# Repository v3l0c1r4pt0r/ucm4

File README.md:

# uCM4

Raspberry Pi Compute Module 4 micro carrier board

# Features

* exactly same size as CM4
* support for both Lite and eMMC variants of CM4
* Gigabit Ethernet
* microSD slot (optional)
* Micro USB for power and USB 2.0 data transfer
* USB-OTG support

# Table of contents

1. [Customizations](customizations.md)
2. [Troubleshooting](troubleshooting.md)

# Project page

Complete project page with pictures, updates and so on, is available at
[Hackaday.io](https://hackaday.io/project/179793-ucm4).

# License

This work is licensed under a [Creative Commons Attribution 4.0 International License][cc-by].

You can use it for anything as long as you preserve license file and author information in source distribution and authorship information on PCB. Derived work should mention original author in same locations as this repository.

[![CC BY 4.0][cc-by-image]][cc-by]

[cc-by]: http://creativecommons.org/licenses/by/4.0/
[cc-by-image]: https://i.creativecommons.org/l/by/4.0/88x31.png

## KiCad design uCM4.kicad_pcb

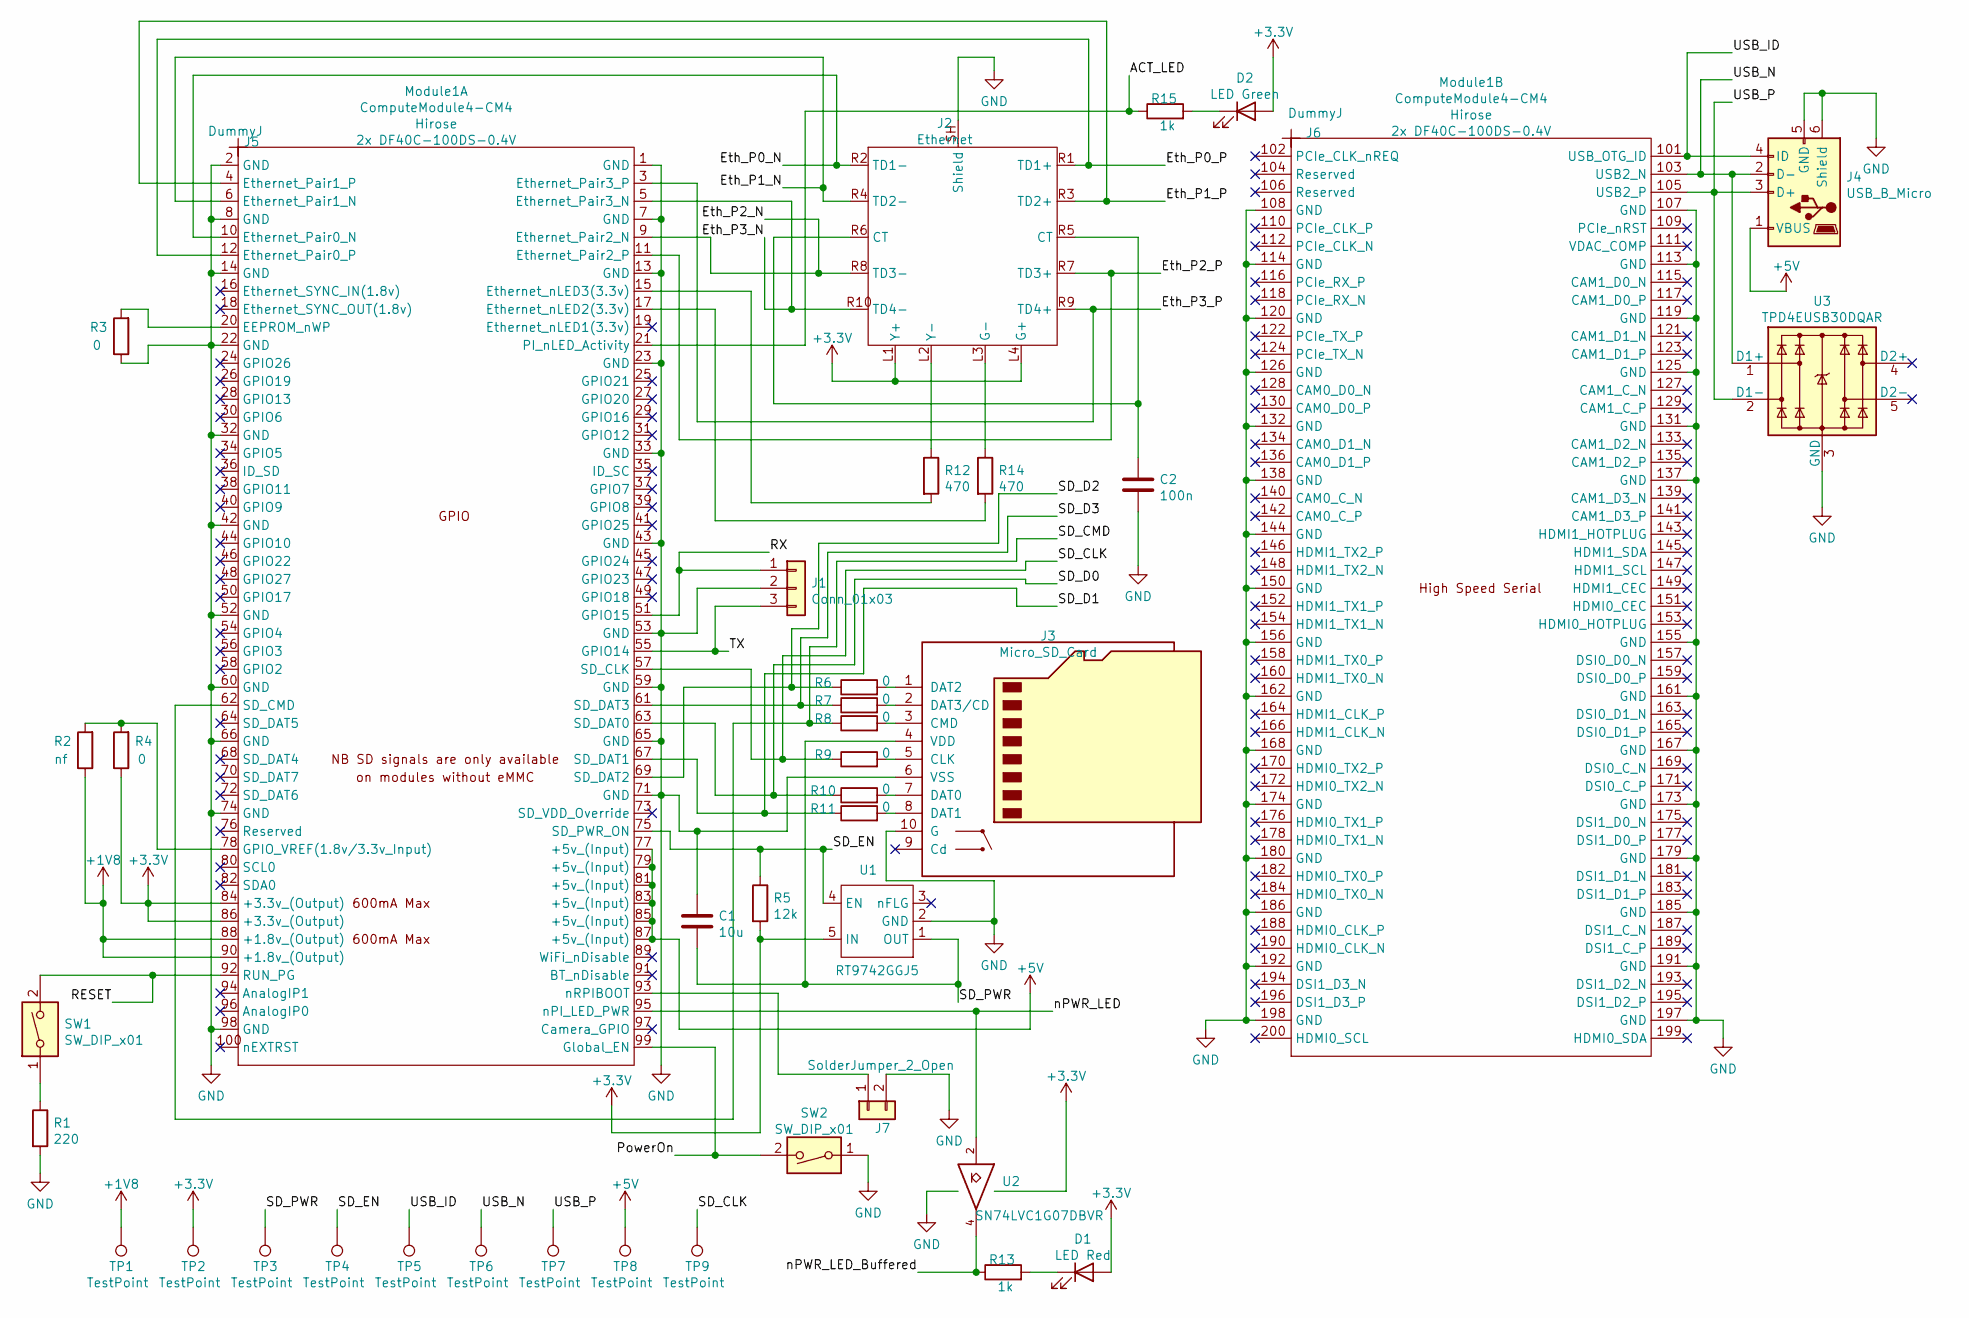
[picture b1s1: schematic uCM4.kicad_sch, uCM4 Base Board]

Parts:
C1: 10u; C_0603_1608Metric_Pad1.08x0.95mm_HandSolder; LCSC# C326057
C2: 100n; C_0603_1608Metric_Pad1.08x0.95mm_HandSolder; LCSC# C108079
D1: LED Red; LED_0603_1608Metric_Pad1.05x0.95mm_HandSolder; LCSC# C181863
D2: LED Green; LED_0603_1608Metric_Pad1.05x0.95mm_HandSolder; LCSC# C72043
J1: Conn_01x03; PinHeader_1x03_P2.54mm_Vertical; LCSC# C49257
J2: Ethernet; RB1-2S5BAK1A; LCSC# C363232
J3: Micro_SD_Card; TF-015; LCSC# C113206
J4: USB_B_Micro; U254-05XX-4BH81; LCSC# C2682232
J5, J6: DummyJ; LCSC# C424649
J7: SolderJumper_2_Open; PinHeader_1x02_P2.54mm_Vertical
Module1: ComputeModule4-CM4; Raspberry-Pi-4-Compute-Module; LCSC# C424649
R1: 220; R_0603_1608Metric_Pad0.98x0.95mm_HandSolder; LCSC# C22962
R2: nf; R_0603_1608Metric_Pad0.98x0.95mm_HandSolder
R3, R4: 0; R_0603_1608Metric_Pad0.98x0.95mm_HandSolder; LCSC# C21189
R5: 12k; R_0603_1608Metric_Pad0.98x0.95mm_HandSolder; LCSC# C22790
R6, R7, R8, R9, R10, R11: 0; R_0402_1005Metric_Pad0.72x0.64mm_HandSolder; LCSC# C17168
R12, R14: 470; R_0603_1608Metric_Pad0.98x0.95mm_HandSolder; LCSC# C23179
R13, R15: 1k; R_0603_1608Metric_Pad0.98x0.95mm_HandSolder; LCSC# C21190
SW1, SW2: SW_DIP_x01; PTS840_PM_SMTR_LFS; LCSC# C221911
TP1, TP2, TP3, TP4, TP5, TP6, TP7, TP8, TP9: TestPoint; TestPoint_Pad_D1.0mm
U1: RT9742GGJ5; SOT-23-5; Part Description Power Switch/Driver 1:1 N-Channel 1A TS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; LCSC# C2693603
U2: SN74LVC1G07DBVR; SOT-23-5_HandSoldering; LCSC# C7829
U3: TPD4EUSB30DQAR; USON-10_2.5x1.0mm_P0.5mm; LCSC# C90627

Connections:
+1V8: Module1.88 (+1.8v_(Output)), Module1.90 (+1.8v_(Output)), R2.1, TP1.1
+3V3: D1.2 (A), D2.2 (A), J2.L1 (Y+), J2.L4 (G+), Module1.84 (+3.3v_(Output)), Module1.86 (+3.3v_(Output)), R4.1, R5.2, TP2.1, U1.5 (IN), U2.5 (VCC)
+5V: J4.1 (VBUS), Module1.77 (+5v_(Input)), Module1.79 (+5v_(Input)), Module1.81 (+5v_(Input)), Module1.83 (+5v_(Input)), Module1.85 (+5v_(Input)), Module1.87 (+5v_(Input)), TP8.1
/ACT_LED: Module1.21 (PI_nLED_Activity), R15.1
/Eth_P0_N: J2.R2 (TD1-), Module1.10 (Ethernet_Pair0_N)
/Eth_P0_P: J2.R1 (TD1+), Module1.12 (Ethernet_Pair0_P)
/Eth_P1_N: J2.R4 (TD2-), Module1.6 (Ethernet_Pair1_N)
/Eth_P1_P: J2.R3 (TD2+), Module1.4 (Ethernet_Pair1_P)
/Eth_P2_N: J2.R8 (TD3-), Module1.9 (Ethernet_Pair2_N)
/Eth_P2_P: J2.R7 (TD3+), Module1.11 (Ethernet_Pair2_P)
/Eth_P3_N: J2.R10 (TD4-), Module1.5 (Ethernet_Pair3_N)
/Eth_P3_P: J2.R9 (TD4+), Module1.3 (Ethernet_Pair3_P)
/PowerOn: Module1.99 (Global_EN), SW2.2
/RESET: Module1.92 (RUN_PG), SW1.2
/RX: J1.1, Module1.51 (GPIO15)
/SD_CLK: Module1.57 (SD_CLK), R9.1, TP9.1
/SD_CMD: Module1.62 (SD_CMD), R8.1
/SD_D0: Module1.63 (SD_DAT0), R10.1
/SD_D1: Module1.67 (SD_DAT1), R11.1
/SD_D2: Module1.69 (SD_DAT2), R6.1
/SD_D3: Module1.61 (SD_DAT3), R7.1
/SD_EN: Module1.75 (SD_PWR_ON), R5.1, TP4.1, U1.4 (EN)
/SD_PWR: C1.2, J3.4 (VDD), TP3.1, U1.1 (OUT)
/TX: J1.3, Module1.55 (GPIO14)
/USB_ID: J4.4 (ID), Module1.101 (USB_OTG_ID), TP5.1
/USB_N: J4.2 (D-), Module1.103 (USB2_N), TP6.1, U3.1 (D1+)
/USB_P: J4.3 (D+), Module1.105 (USB2_P), TP7.1, U3.2 (D1-)
/nPWR_LED: Module1.95 (nPI_LED_PWR), U2.2
/nPWR_LED_Buffered: R13.1, U2.4
GND: C1.1, C2.2, J1.2, J2.SH (Shield), J3.6 (VSS), J3.10 (G), J4.5 (GND), J4.6 (Shield), J7.2, Module1.1 (GND), Module1.2 (GND), Module1.7 (GND), Module1.8 (GND), Module1.13 (GND), Module1.14 (GND), Module1.22 (GND), Module1.23 (GND), Module1.32 (GND), Module1.33 (GND), Module1.42 (GND), Module1.43 (GND), Module1.52 (GND), Module1.53 (GND), Module1.59 (GND), Module1.60 (GND), Module1.65 (GND), Module1.66 (GND), Module1.71 (GND), Module1.74 (GND), Module1.98 (GND), Module1.107 (GND), Module1.108 (GND), Module1.113 (GND), Module1.114 (GND), Module1.119 (GND), Module1.120 (GND), Module1.125 (GND), Module1.126 (GND), Module1.131 (GND), Module1.132 (GND), Module1.137 (GND), Module1.138 (GND), Module1.144 (GND), Module1.150 (GND), Module1.155 (GND), Module1.156 (GND), Module1.161 (GND), Module1.162 (GND), Module1.167 (GND), Module1.168 (GND), Module1.173 (GND), Module1.174 (GND), Module1.179 (GND), Module1.180 (GND), Module1.185 (GND), Module1.186 (GND), Module1.191 (GND), Module1.192 (GND), Module1.197 (GND), Module1.198 (GND), R1.2, R3.1, SW2.1, U1.2 (GND), U2.3 (GND), U3.3 (GND), U3.8 (GND)
unnamed: C2.1, J2.R5 (CT), J2.R6 (CT)
unnamed: D1.1 (K), R13.2
unnamed: D2.1 (K), R15.2
unnamed: J2.L2 (Y-), R12.1
unnamed: J2.L3 (G-), R14.1
unnamed: J3.1 (DAT2), R6.2
unnamed: J3.2 (DAT3/CD), R7.2
unnamed: J3.3 (CMD), R8.2
unnamed: J3.5 (CLK), R9.2
unnamed: J3.7 (DAT0), R10.2
unnamed: J3.8 (DAT1), R11.2
unnamed: J7.1, Module1.93 (nRPIBOOT)
unnamed: Module1.15 (Ethernet_nLED3(3.3v)), R12.2
unnamed: Module1.17 (Ethernet_nLED2(3.3v)), R14.2
unnamed: Module1.20 (EEPROM_nWP), R3.2
unnamed: Module1.78 (GPIO_VREF(1.8v/3.3v_Input)), R2.2, R4.2
unnamed: R1.1, SW1.1

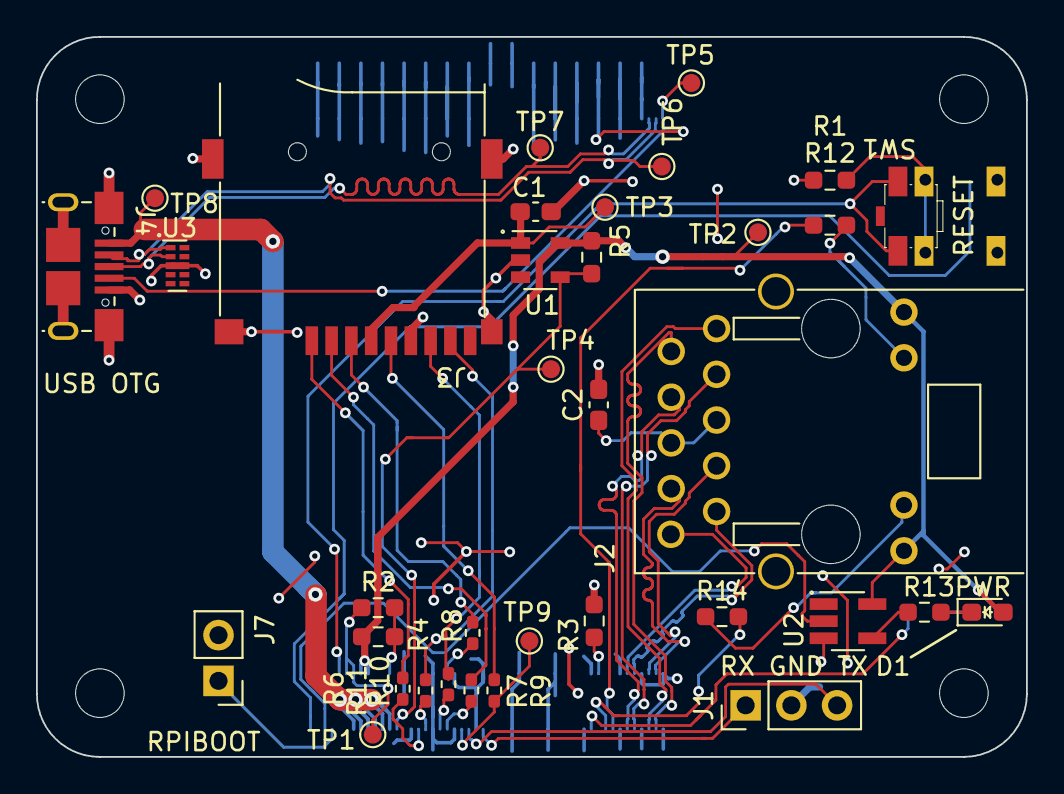
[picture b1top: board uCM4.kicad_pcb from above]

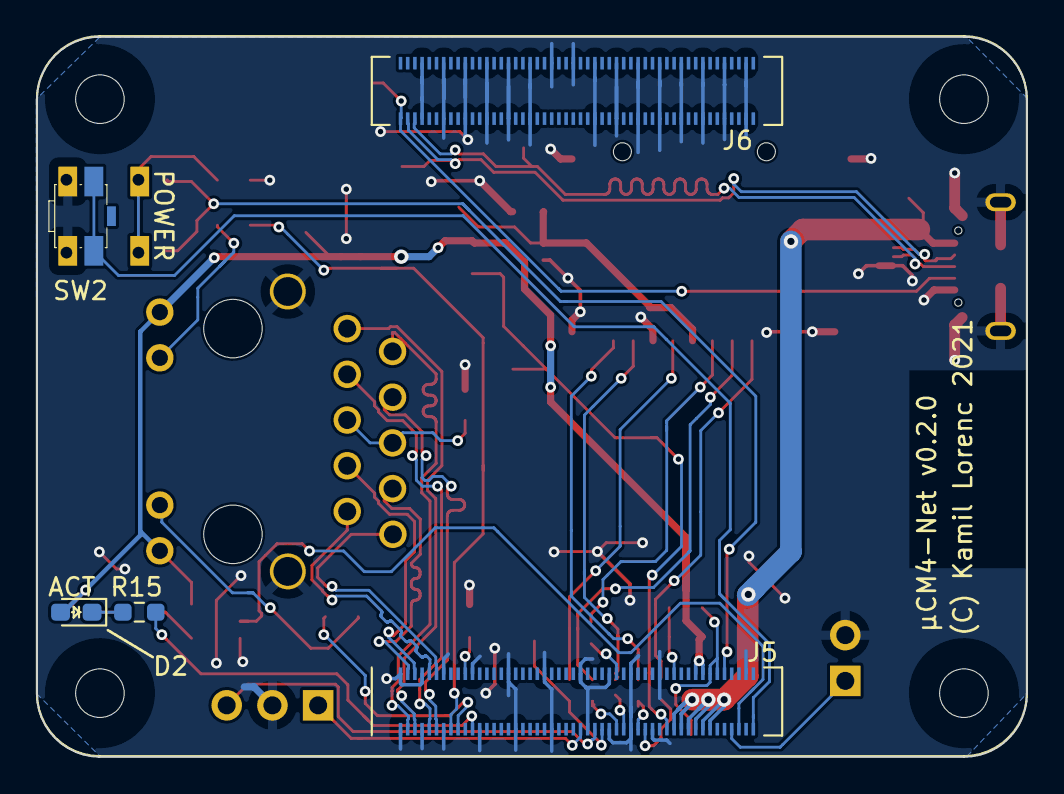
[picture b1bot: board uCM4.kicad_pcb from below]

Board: 2 copper layers, 55.0 x 40.0 mm, 41 parts (6 on the bottom side), 47 nets.

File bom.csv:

"Comment","Designator","Footprint","LCSC Part #"
"10u","C1","0603_C","C19702"
"100n","C2","0603_C","C14663"
"red","D1","LED_0603","C2286"
"green","D2","LED_0603","C72043"
"220","R1","0603","C22962"
"0","R3","0603","C21189"
"0","R4","0603","C21189"
"12k","R5","0603","C22790"
"0","R6","0402","C17168"
"0","R7","0402","C17168"
"0","R8","0402","C17168"
"0","R9","0402","C17168"
"0","R10","0402","C17168"
"0","R11","0402","C17168"
"470","R12","0603","C23179"
"1k","R13","0603","C21190"
"470","R14","0603","C23179"
"1k","R15","0603","C21190"
"","U1","TSOT-23-5","C2693603"
"","U2","SOT-353","C67531"
"","U3","USON-10","C558427"

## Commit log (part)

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2021-03-20 Initial empty repository
2021-03-20 Start development
    Add library from CM4IO, place CM4 and set edge cuts. Ignore unneeded
    files.
2021-03-27 Implement missing parts of schematics
    Add LEDs, ESD protection on USB connector and mark some pins as unused.
    What is left for considerations is implementing RTC. Maybe Ethernet has
    to be converted to bus, as wires within a pair has to be same length.
2021-03-28 Add MicroUSB connector
    Unfinished, but functional.
2021-03-28 Connect GNDs to ground
    Was overlooked in high-speed connector.
2021-03-28 Attempt to fix shield of Eth
    Just a rename from Shield to SH. Seems to be failed. But, who knows.
2021-03-28 Connect power of 74* buffer
    It was missing till now. Also update PCB to reflect changes.
2021-03-28 Finalize MicroUSB receptacle footprint
    Now everything is finished, including PCB edge indicator and outline.
    Helper lines are still there, in case, modification is required.
2021-03-28 Update MicroUSB on PCB
2021-04-03 Add new Ethernet connector
    Will eventually replace old one, as this one is available, while old
    would have to be backordered.
2021-04-03 Fix electrical connections of Eth
    Old Ethernet connector had different pin meaning, despite almost same
    footprint. Update schematics to match new connector.
2021-04-03 Add net names for Ethernet
    Is required to setup differential pairs.
2021-04-03 Configure DP router
    Reconfigure board rules to allow routing differential pairs.
2021-04-03 Make USB differential
    Rename net to allow differential routing
2021-04-03 Route USB connection
    Not adjusted length yet.
2021-04-03 Start routing power buses
    Most likely not the target way to do that, but just to indicate the
    problem.
2021-04-03 Name some signals on schematics
    Makes reading PCB easier.
2021-04-03 Route secondary power rail
    3V3
2021-04-04 Connect shield on Micro USB connector
    This was the last error when updating PCB from schematics.
2021-04-04 Eliminate problems on Ethernet connector
2021-04-04 Fix errors on Micro USB connector
    Is now all fine.
2021-04-04 Reroute USB pair
    Should now be DRC error-free.
2021-04-04 Attempt at writing JLCPCB rules
    As custom rules. Will see if this is better, as not always rule can be
    fitted into table.
2021-04-04 Cleanup Eth connector
    Remove all measuring lines on User.Drawing layer. This makes footprint
    production-ready.
2021-04-04 Fix error with Micro SD silkscreen
2021-04-04 Remove all routining beside main power rail
    5V rail should be fine, as it keeps distance from faulty sections and
    chances are Micro USB (and Hirose) will stay at their places.
2021-04-04 Remove notes from Eth connector
    Remove all lines on User.Drawings layer that were used for designing and
    checking the connector footprint.
2021-04-04 Draw stands on Micro SD connector
    It conflicts with mounting hole and this is the only problem on the
    whole board at the moment. There are two ways to solve this, as it is
    the only place where it (almost) fits:
    1. Make ground plane of Micro SD a bit smaller - in the worst case will
    not mount connector to PCB
    2. Remove mounting hole of module - will make two boards a little bit
2021-04-07 Reroute Ethernet and suroundings
    All traces intersecting with Ethernet had to be removed to make
    rerouting easier. Then Ethernet pairs were routed again. No length
    adjustments has been done yet.
2021-04-07 Fix zeroth Ethernet pair
    Now it is in tolerance. Now it is a question, if another attempt for
    pair-to-pair difference reduction makes any sense.
2021-04-10 Recreate all deleted traces
    During Ethernet rerouting, some other traces were deleted. Create them
    from scratch. Now board seem to be lacking only ground plane and its
    connections.
2021-04-10 Reduce error count
    Some unconnected pads were possible to connect.
2021-04-11 I don't remember what
2021-04-11 Add courtyard around Eth commector
    Set to 1.25mm - is maximum courtyard specified by JLCPCB. Will see if
    this would be final.
2021-04-11 Set Eth courtyard to 0.5mm
2021-04-13 Add courtyard for Micro SD slot
2021-04-13 Fix Micro USB courtyard and fab layer
    Updates based on physical view of the connector.
2021-04-13 Fix various DRC errors
    Setting courtyards revealed some minor problems.
2021-04-13 Fix Ethernet shield
    Symbol had shield pin unnamed, therefore there was no connection between
    it and PCB. Naming, updating symbol and footprint, the redoing DRC fixed
    the issue.
2021-04-14 Do small improvements to traces
2021-04-14 Cleanup
2021-04-16 Fix pad-NPTH conflict on Micro USB connector
2021-04-16 Micro USB: Fix silkscreen footprint
2021-04-16 Increase margin on Micro USB
2021-04-16 Remove CM4 outline from silkscreen
    It was at the same location as edge cuts, so would be broken.
2021-04-16 Move some silkscreen markings
    Cosmetic changes for first release to manufacturing.
2021-04-16 Remove drill files
    Committed by accident.
2021-04-17 Ignore some more files
2021-04-17 Add outline of BCM SoC on CM4
    Makes mounting easier
2021-04-17 Fix hole-silkscreen conflict
2021-04-17 I don't know what
2021-05-20 Change location of TP5
    I thought it was the reason for no via going to it. The real reason
    turned out to be forgetting to regenerate drill files. Nevertheless it
    does not harm, so let's leave it as it is.
    Done as a result of #1.
2021-05-23 Add troubleshooting guide
2021-07-04 Create LICENSE
2021-07-04 README: add licensing conditions
2021-07-12 Add PCB v0.1.0 render
2021-07-13 Do not tent vias
    For development is perfectly fine. Might cause issue, when via is close
    to a pad. This is the only improvement that can be done in context of
    issue #6.
2021-07-13 Link KiCAD_Randoms to the project
2021-07-13 Add CM4IO-KiCAD as submodule
    Specially for that purpose, I created repo on Github with it. Add it as
    submodule to allow it to be linked relative to ${KIPRJMOD} in KiCAD
    settings.
2021-07-13 Bump version on PCB to 0.1.1
2021-07-13 Remove unused Connector_RJ library
    Most likely was attempted to use it for Ethernet connector, but never
    succeeded in this. And contained absolute path to directory, which no
    other user beside me has.
2021-07-13 Move J2 label back to its original position
    This is a bug caused by changing Ethernet footprint to different
    library.
2021-07-14 Add make targets for autogenerating BOM and CPL
    Use AWK to convert uCM4-top-pos.csv file into formats acceptable by
    JLCPCB. Almost fully automates the process, as still there are no LCSC
    part numbers, so all parts would have to be selected manually.
2021-07-15 Import BOM script from KiCAD
    Will be modified to match JLCPCB output format also with LCSC part
    number.
2021-07-15 Output in format desired by JLCPCB
2021-07-15 Print metadata only in DEBUG mode
    Turned on by setting DEBUG=1 in environment.
2021-07-15 Fill LCSC part numbers for connectors
2021-07-16 Add BOM and CPL for bottom side
    Should allow soldering Hirose on JLCPCB. This seems to be really cost
    and labour effective way of assembling the board - just around $3
    additional costs.
2021-08-13 Bump to version 0.2.0
2021-08-13 Make preparations for required changes in 0.2.0
    Following has been performed and could not be made separately:
    - move LEDs to smaller space next to Ethernet
    - move buttons to bigger space next to Ethernet
    - two changes above makes together handy interface for whole board,
    where almost everything needed is on one side
    - move all parts belonging to LEDs and buttons near their new locations
2021-08-13 Update footprint for buttons
    Now should point to almost finished PTS840.
2021-08-13 Some small adjustments
    Nothing important.
2021-08-25 Update PCB after schematics changes
    Most significantly LCSC# and some part names. Nothing important from PCB
    perspective, despite amount of changes.
2021-08-25 Move label of buffer chip
2021-08-25 One more fix
    Ignore. Nothing important.
2021-08-26 Random stuff
    Have no idea what this is.
2021-08-26 Fix most obvious 6mil clearance errors
    Beside signal buses - USB and Ethernets, almost everything is fine now.
2021-08-26 Remove TODO
    5V is already here. I don't know why I wrote that :)
2021-08-27 Match ethernet trace lengths
2021-08-29 Adjust USB connector to 6mil constraint
    Now it passes DRC.
2021-08-29 Adjust TVS diode footprint to fix DRC errors
    Pads must be slightly smaller to fit into 6 mils limit (~0.02 mm
    smaller). Should not harm.
2021-08-29 Route USB
    Differential pair. No length adjustment done yet.
2021-08-29 Reconnect SD's D2 and GDN on pin 71
    Lack of connection from pin 71 on low speed connector was last problem
    that DRC reported. By the way via for D2 has to be moved to allow
    track from GND go its way. At this point DRC is green.
2021-08-29 Swap sides for power and reset button
    It is more convenient to have reset on top, as it is not at the edge of
    board. Also it decreases a risk of damage to CM4, as it may happen
    someone will try to reset with conductive, metal thing and touch
    something on CM4. Having power button on bottom (CM4) side does not pose
    that risk as it is exactly at the edge.
2021-08-29 Tent vias again
    Not tenting them makes assembly harder, when done manually. When machine
    does that, it may simply fail by making short or something.
2021-09-04 Connect ground planes
2021-09-05 Update kicad randoms
2021-09-05 Update kicad-randoms for designator changes
2021-09-05 Make a lot of small changes for RFM
    Release for Manufacturing require some otherwise not important details
    to be correctly set. These include manufacturer part numbers for BOM,
    origin point being set, designators on fab layer for PDF generation.
    When assembly was done on JLCPCB, only custom pick&place file and BOM,
    almost auto-generated was important. For more traditional factory, more
    work needs to be done. This commit fixes a lot of such small things.
2021-09-05 Remove BOM and P&P files
    They are not up to date anymore.
2021-09-06 Change track widths to >6mil
    Most of the tracks could be changed to 0.16 mm straight away. Some
    generated clearance violation. But generally, besides Ethernet, which is
    always a problem, should not be so hard to fix.
2021-09-07 Fix TVS diode footprint to fit into clearance
    Clearance should be at least 6mils (~1.6 mm). This should not cause
    problems with soldering (hopefully).
2021-09-07 Make ground plane on USB connector smaller
    Now it fits into >6mils constraint for clearance.
2021-09-07 Modify keepout of Ethernet and connect tracks
    Keepout area does not have to forbid tracks from appearing under it.
    Remove this constraint and connect last missing track. Now all errors,
    beside Ethernet are fixed.
2021-09-07 Redo Ethernet tracks
    Now DRC passes on 0,16 mm setting. Ethernet length matching not done
    yet.
2021-09-07 Reset origin point
    Let it be 2mm to the left and down from virtual left-bottom corner.
2021-09-08 Add courtyard to dummy Hirose J
    Dummy Hirose entities must have proper center point, so they can be
    mounted properly at the factory site. Add courtyard based on the
    silkscreen layer for real connectors. Do it on user drawings, so nobody
    will use this footprint further.
2021-09-08 Couple fixes on fab layer
    Nothing really important. Might be useful for boardview.
2021-09-09 Change footprint for rpiboot
    Now it is standard 2.54 2-pin header. Will not be populated in fab by
    default!
2021-09-11 Remove Makefile for gerbers
    They were not the most useful setup anyway. To generate proper gerber
    distribution one had to generate Gerbers and drill files manually, from
    KiCAD. Then they could be packed into proper zips by the makefile. At
    least once it led to accidental lack of drill files update.
2021-09-11 Set red LED to everlight
    112 mcd max - perfect!
2021-09-12 Various different fixes on PCB
    There was incorrect footprint committed for J3 and J4. Now I don't know
    what else changed with this commit.
2021-09-12 Add next diode direction indicator
2021-09-12 Fix ground size on J4
